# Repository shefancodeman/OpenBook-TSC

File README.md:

# TSC Openbook
 Un eBook reader format din PCB, carcasa, baterie si display, creat in AutoDesk Fusion. Fiecare component e asezat pe pcb pentru a intra corespunzator in carcasa.  
PCB-ul include:
- Battery Charge Level  
- E-Paper Display Header  
- E-Paper Drive Circuit  
- Environmental Sensor BME688  
- EPD Power  
- ESP32 C6  
- External NOR Flash 64MB  
- LDO Voltage Regulator  
- Li-Po Battery Charging Controller  
- Qwiic / Stemma QT  
- RTC Module DS3231SN  
- SD Card  
- SPI ESD Protection Lines  
- Test Pads  
- USB C connector & ESD protection  
- Voltage Supervisor + Reset & Boot / IO Button  

## BOM
| Component                     | Websites                                                                                                   | Datasheet                                                                                                    |
|-------------------------------|------------------------------------------------------------------------------------------------------------|------------------------------------------------------------------------------------------------------------|
| ESP32-C6-WROOM-1-N8           | [Mouser](https://eu.mouser.com/ProductDetail/Espressif-Systems/ESP32-C6-WROOM-1U-N8?qs=1Kr7Jg1SGW%2FzPU4G%252ByMwkA%3D%3D) | [Datasheet](https://eu.mouser.com/datasheet/2/891/Espressif_Systems_7_11_2023_esp32_c6_wroom_1_wroom-3236277.pdf) |
| USB4110-GF-A                  | [Mouser](https://eu.mouser.com/ProductDetail/Same-Sky/UJC-H-G-SMT-2-P6-TR?qs=IKkN%2F947nfApFV8T6rOqww%3D%3D) | [Datasheet](https://eu.mouser.com/datasheet/2/1628/ujc_h_g_smt_2_p6_tr-3511211.pdf)                          |
| USBLC6-2SC6Y                  | [Mouser](https://eu.mouser.com/ProductDetail/STMicroelectronics/USBLC6-2SC6Y?qs=gNDSiZmRJS%2FOgDexvXkdow%3D%3D) | [Datasheet](https://eu.mouser.com/datasheet/2/389/usblc6_2sc6y-1852505.pdf)                                   |
| DMG2305UX-7                   | [Mouser](https://eu.mouser.com/ProductDetail/Diodes-Incorporated/DMG2305UX-7?qs=L1DZKBg7t5F%2FNBHrjfxC%252Bg%3D%3D) | [Datasheet](https://www.diodes.com/assets/Datasheets/DMG2305UX.pdf)                                           |
| SD0805S020S1R0                | [Mouser](https://eu.mouser.com/ProductDetail/KYOCERA-AVX/SD0805S020S1R0?qs=jCA%252BPfw4LHbpkAoSnwrdjw%3D%3D) | [Datasheet](https://eu.mouser.com/datasheet/2/40/schottky-3165252.pdf)                                       |
| XC6220A331MR-G                | [Mouser](https://eu.mouser.com/ProductDetail/Torex-Semiconductor/XC6220A331MR-G?qs=AsjdqWjXhJ8ZSWznL1J0gg%3D%3D) | [Datasheet](https://eu.mouser.com/datasheet/2/760/xc6220-3371556.pdf)                                         |
| 293D107X9010D2TE3             | [Mouser](https://eu.mouser.com/ProductDetail/Vishay-Sprague/293D107X9010D2TE3?qs=8dfOI6wKXonVqFgS8%252BQ%2FMA%3D%3D) | [Datasheet](https://www.vishay.com/docs/40002/293d.pdf)                                                       |
| IFDC5050JZER680M              | [Mouser](https://eu.mouser.com/ProductDetail/Vishay-Dale/IFDC5050JZER680M?qs=iLKYxzqNS745SePZd8tBoA%3D%3D) | [Datasheet](https://www.vishay.com/docs/34635/ifdc5050jz.pdf)                                                |
| MBR0530-TP                    | [Mouser](https://eu.mouser.com/ProductDetail/Micro-Commercial-Components-MCC/MBR0530-TP?qs=KFo7JewZbUECRHkxGanrdg%3D%3D) | [Datasheet](https://eu.mouser.com/datasheet/2/258/MBR0520_MBR0580_SOD123_-2492194.pdf)                      |
| SI1308EDL-T1-GE3              | [Mouser](https://eu.mouser.com/ProductDetail/Vishay-Semiconductors/SI1308EDL-T1-GE3?qs=bX1%252BNvsK%2FBramh9tgpOaEw%3D%3D) | [Datasheet](https://www.vishay.com/docs/63399/si1308edl.pdf)                                                |
| KGF21BR71H104KT               | [Mouser](https://eu.mouser.com/ProductDetail/KYOCERA-AVX/KGF21BR71H104KT?qs=Jm2GQyTW%2FbjYyKCvVWAEOw%3D%3D) | [Datasheet](https://eu.mouser.com/datasheet/2/40/KGF-3223650.pdf)                                            |
| MAASL105CC7105MFCA01          | [Mouser](https://eu.mouser.com/ProductDetail/TAIYO-YUDEN/MAASL105CC7105MFCA01?qs=HFfMDpzxxd1Fn%2FInbJA7vw%3D%3D) | [Datasheet](https://eu.mouser.com/datasheet/2/396/TAIYO_YUDEN_04_27_2024_c_mlcc_A_e1-3451516.pdf)           |
| CM05X5R475M16AH               | [Mouser](https://eu.mouser.com/ProductDetail/KYOCERA-AVX/CM05X5R475M16AH?qs=doiCPypUmgFT1xquZKhWtQ%3D%3D) | [Datasheet](https://eu.mouser.com/datasheet/2/40/Kyocera_AVX_Components_CM025_CM05_CM105_CM21_E217K-2932876.pdf) |
| CGA3EDX7T1A106M080AU          | [Mouser](https://eu.mouser.com/ProductDetail/TDK/CGA3EDX7T1A106M080AU?qs=ZcfC38r4PovL%2FBNBUzzBFw%3D%3D) | [Datasheet](https://product.tdk.com/system/files/dam/doc/product/capacitor/ceramic/mlcc/catalog/mlcc_automotive_general_en.pdf) |
| KAM21BR71H104JT               | [Mouser](https://eu.mouser.com/ProductDetail/KYOCERA-AVX/KAM21BR71H104JT?qs=Jm2GQyTW%2Fbic6Zk4McEt6w%3D%3D) | [Datasheet](https://eu.mouser.com/datasheet/2/40/AutoMLCCKAM-3216307.pdf)                                    |
| RNCL1210FT50L0                | [Mouser](https://eu.mouser.com/ProductDetail/SEI-Stackpole/RNCL1210FT50L0?qs=17ckDYBRdelVLOJ%252BDFjlUw%3D%3D) | [Datasheet](https://eu.mouser.com/datasheet/2/385/sei_rncl-3223524.pdf)                                      |
| RT1206FRE072R2L               | [Mouser](https://eu.mouser.com/ProductDetail/YAGEO/RT1206FRE072R2L?qs=XhSZopxZ3H6S0nYZD83pAA%3D%3D) | [Datasheet](https://eu.mouser.com/datasheet/2/447/PYu_RT_1_to_0_01_RoHS_L_15-3461507.pdf)                    |
| ERA-6AHD150V                  | [Mouser](https://eu.mouser.com/ProductDetail/Panasonic/ERA-6AHD150V?qs=MNPzkKEzRtQip8ZeekU%252BRw%3D%3D) | [Datasheet](https://industrial.panasonic.com/cdbs/www-data/pdf/RDM0000/AOA0000C307.pdf)                     |
| RP73C2B200RFTDF               | [Mouser](https://eu.mouser.com/ProductDetail/TE-Connectivity-Holsworthy/RP73C2B200RFTDF?qs=n4i9pByFsMR0dWGpf721CA%3D%3D) | [Datasheet](https://eu.mouser.com/datasheet/2/418/10/ENG_DS_1773272_M1-1588495.pdf)                          |
| ERA-3AED202V                  | [Mouser](https://eu.mouser.com/ProductDetail/Panasonic/ERA-3AED202V?qs=yocZuyCaXdM2cBmjcGkIyA%3D%3D) | [Datasheet](https://industrial.panasonic.com/cdbs/www-data/pdf/RDM0000/AOA0000C307.pdf)                     |
| MCS04020C5101FE000            | [Mouser](https://eu.mouser.com/ProductDetail/Vishay-Beyschlag/MCS04020C5101FE000?qs=wTZ%2FFzl837YsKPLPRIXUbg%3D%3D) | [Datasheet](https://www.vishay.com/docs/28705/mcx0x0xpro.pdf)                                               |
| RNWA0612BTE10K0               | [Mouser](https://eu.mouser.com/ProductDetail/SEI-Stackpole/RNWA0612BTE10K0?qs=IKkN%2F947nfD62pDKWE9ZTQ%3D%3D) | [Datasheet](https://eu.mouser.com/datasheet/2/385/SEI_RNWA-3473840.pdf)                                      |
| ERA-3AED104V                  | [Mouser](https://eu.mouser.com/ProductDetail/Panasonic/ERA-3AED104V?qs=MNPzkKEzRtQIWcmUWL4kjg%3D%3D) | [Datasheet](https://industrial.panasonic.com/cdbs/www-data/pdf/RDM0000/AOA0000C307.pdf)                     |
| MCP73831-2ACI-MC              | [Mouser](https://eu.mouser.com/ProductDetail/Microchip-Technology/MCP73831-2ACI-MC?qs=hH%252BOa0VZEiBneYTVdpuVdg%3D%3D) | [Datasheet](https://eu.mouser.com/datasheet/2/268/MCP73831_Family_Data_Sheet_DS20001984H-3441711.pdf)       |
| FH34SRJ-24S-0.5SH(99)         | [Mouser](https://eu.mouser.com/ProductDetail/Hirose-Connector/FH34SRJ-24S-0.5SH99?qs=vcbW%252B4%252BSTIpKBl5ap9J8Fw%3D%3D) | [Datasheet](https://eu.mouser.com/datasheet/2/185/FH34SRJ_24S_0_5SH_99__CL0580_1255_6_99_2DDrawing_0-1615044.pdf) |
| BME688                        | [Mouser](https://eu.mouser.com/ProductDetail/Bosch-Sensortec/BME688?qs=IS%252B4QmGtzzqQoVDscqwx3A%3D%3D) | [Datasheet](https://eu.mouser.com/datasheet/2/783/bst_bme688_fl000-2307034.pdf)                              |
| BD5229G-TR                    | [Mouser](https://eu.mouser.com/ProductDetail/ROHM-Semiconductor/BD5229G-TR?qs=4kLU8WoGk0vvnhrrYwdszw%3D%3D) | [Datasheet](https://fscdn.rohm.com/en/products/databook/datasheet/ic/power/voltage_detector/bd52xxg-e.pdf)  |
| MAX17048G+T10                 | [Mouser](https://eu.mouser.com/ProductDetail/Analog-Devices-Maxim-Integrated/MAX17048G%2bT10?qs=D7PJwyCwLAoGnnn8jEPRBQ%3D%3D) | [Datasheet](https://eu.mouser.com/datasheet/2/609/MAX17048_MAX17049-3469099.pdf)                             |
| DS3231SN#                     | [Mouser](https://eu.mouser.com/ProductDetail/Analog-Devices-Maxim-Integrated/DS3231SN?qs=1eQvB6Dk1vhUlr8%2FOrV0Fw%3D%3D) | [Datasheet](https://eu.mouser.com/datasheet/2/609/DS3231-3421123.pdf)                                        |
| CPH3225A                      | [Mouser](https://eu.mouser.com/ProductDetail/Seiko-Semiconductors/CPH3225A?qs=3etwrb1wR%252BhUOph6lAO7eg%3D%3D) | [Datasheet](https://eu.mouser.com/datasheet/2/360/Seiko_Instruments_MicroBattery_E_20230330_2024Jan_-3561061.pdf) |
| PRT-14417                     | [Mouser](https://eu.mouser.com/ProductDetail/Adafruit/4208?qs=PzGy0jfpSMtbScLbr0L5dw%3D%3D) | [Datasheet](https://learn.adafruit.com/introducing-adafruit-stemma-qt/technical-specs)                      |
| PGB1010603MR                  | [Mouser](https://eu.mouser.com/ProductDetail/Littelfuse/PGB1010603MR?qs=gu7KAQ731URLg4GSnNNN7Q%3D%3D) | [Datasheet](https://www.littelfuse.com/assetdocs/pulseguard-esd-suppressors-pgb1-datasheet?assetguid=8a337998-d54d-466b-be4e-dc5bcd1f9321) |
| W25Q512JVEIQ                  | [Mouser](https://eu.mouser.com/ProductDetail/Winbond/W25Q512JVEIQ?qs=l7cgNqFNU1jw6svr3at6tA%3D%3D) | [Datasheet](https://eu.mouser.com/datasheet/2/949/Winbond_W25Q512JV_Datasheet-3240039.pdf)                   |
| MT-DEPG0750BNU590F1           | [Mouser](https://eu.mouser.com/ProductDetail/Microtips-Technology/MT-DEPG0750BNU590F1?qs=DPoM0jnrROVRMMTX0WzK%252Bw%3D%3D) | [Datasheet](https://eu.mouser.com/datasheet/2/271/MT_DEPG0750BNU590F1_V2_7-1894282.pdf)                     |
| 112A-TAAR-R03                 | [Comet](https://store.comet.srl.ro/Catalogue/Product/43497/)                                               | [Datasheet](https://store.comet.bg/download-file.php?id=27596)                                                |
| LP584174                      | [TME](https://www.tme.eu/en/details/accu-lp584174_cl/rechargeable-batteries/cellevia-batteries/l584174/) | [Datasheet](https://www.tme.eu/Document/e0683d8c34e6d878124489f71bffb6ee/cel0014.pdf)                        |

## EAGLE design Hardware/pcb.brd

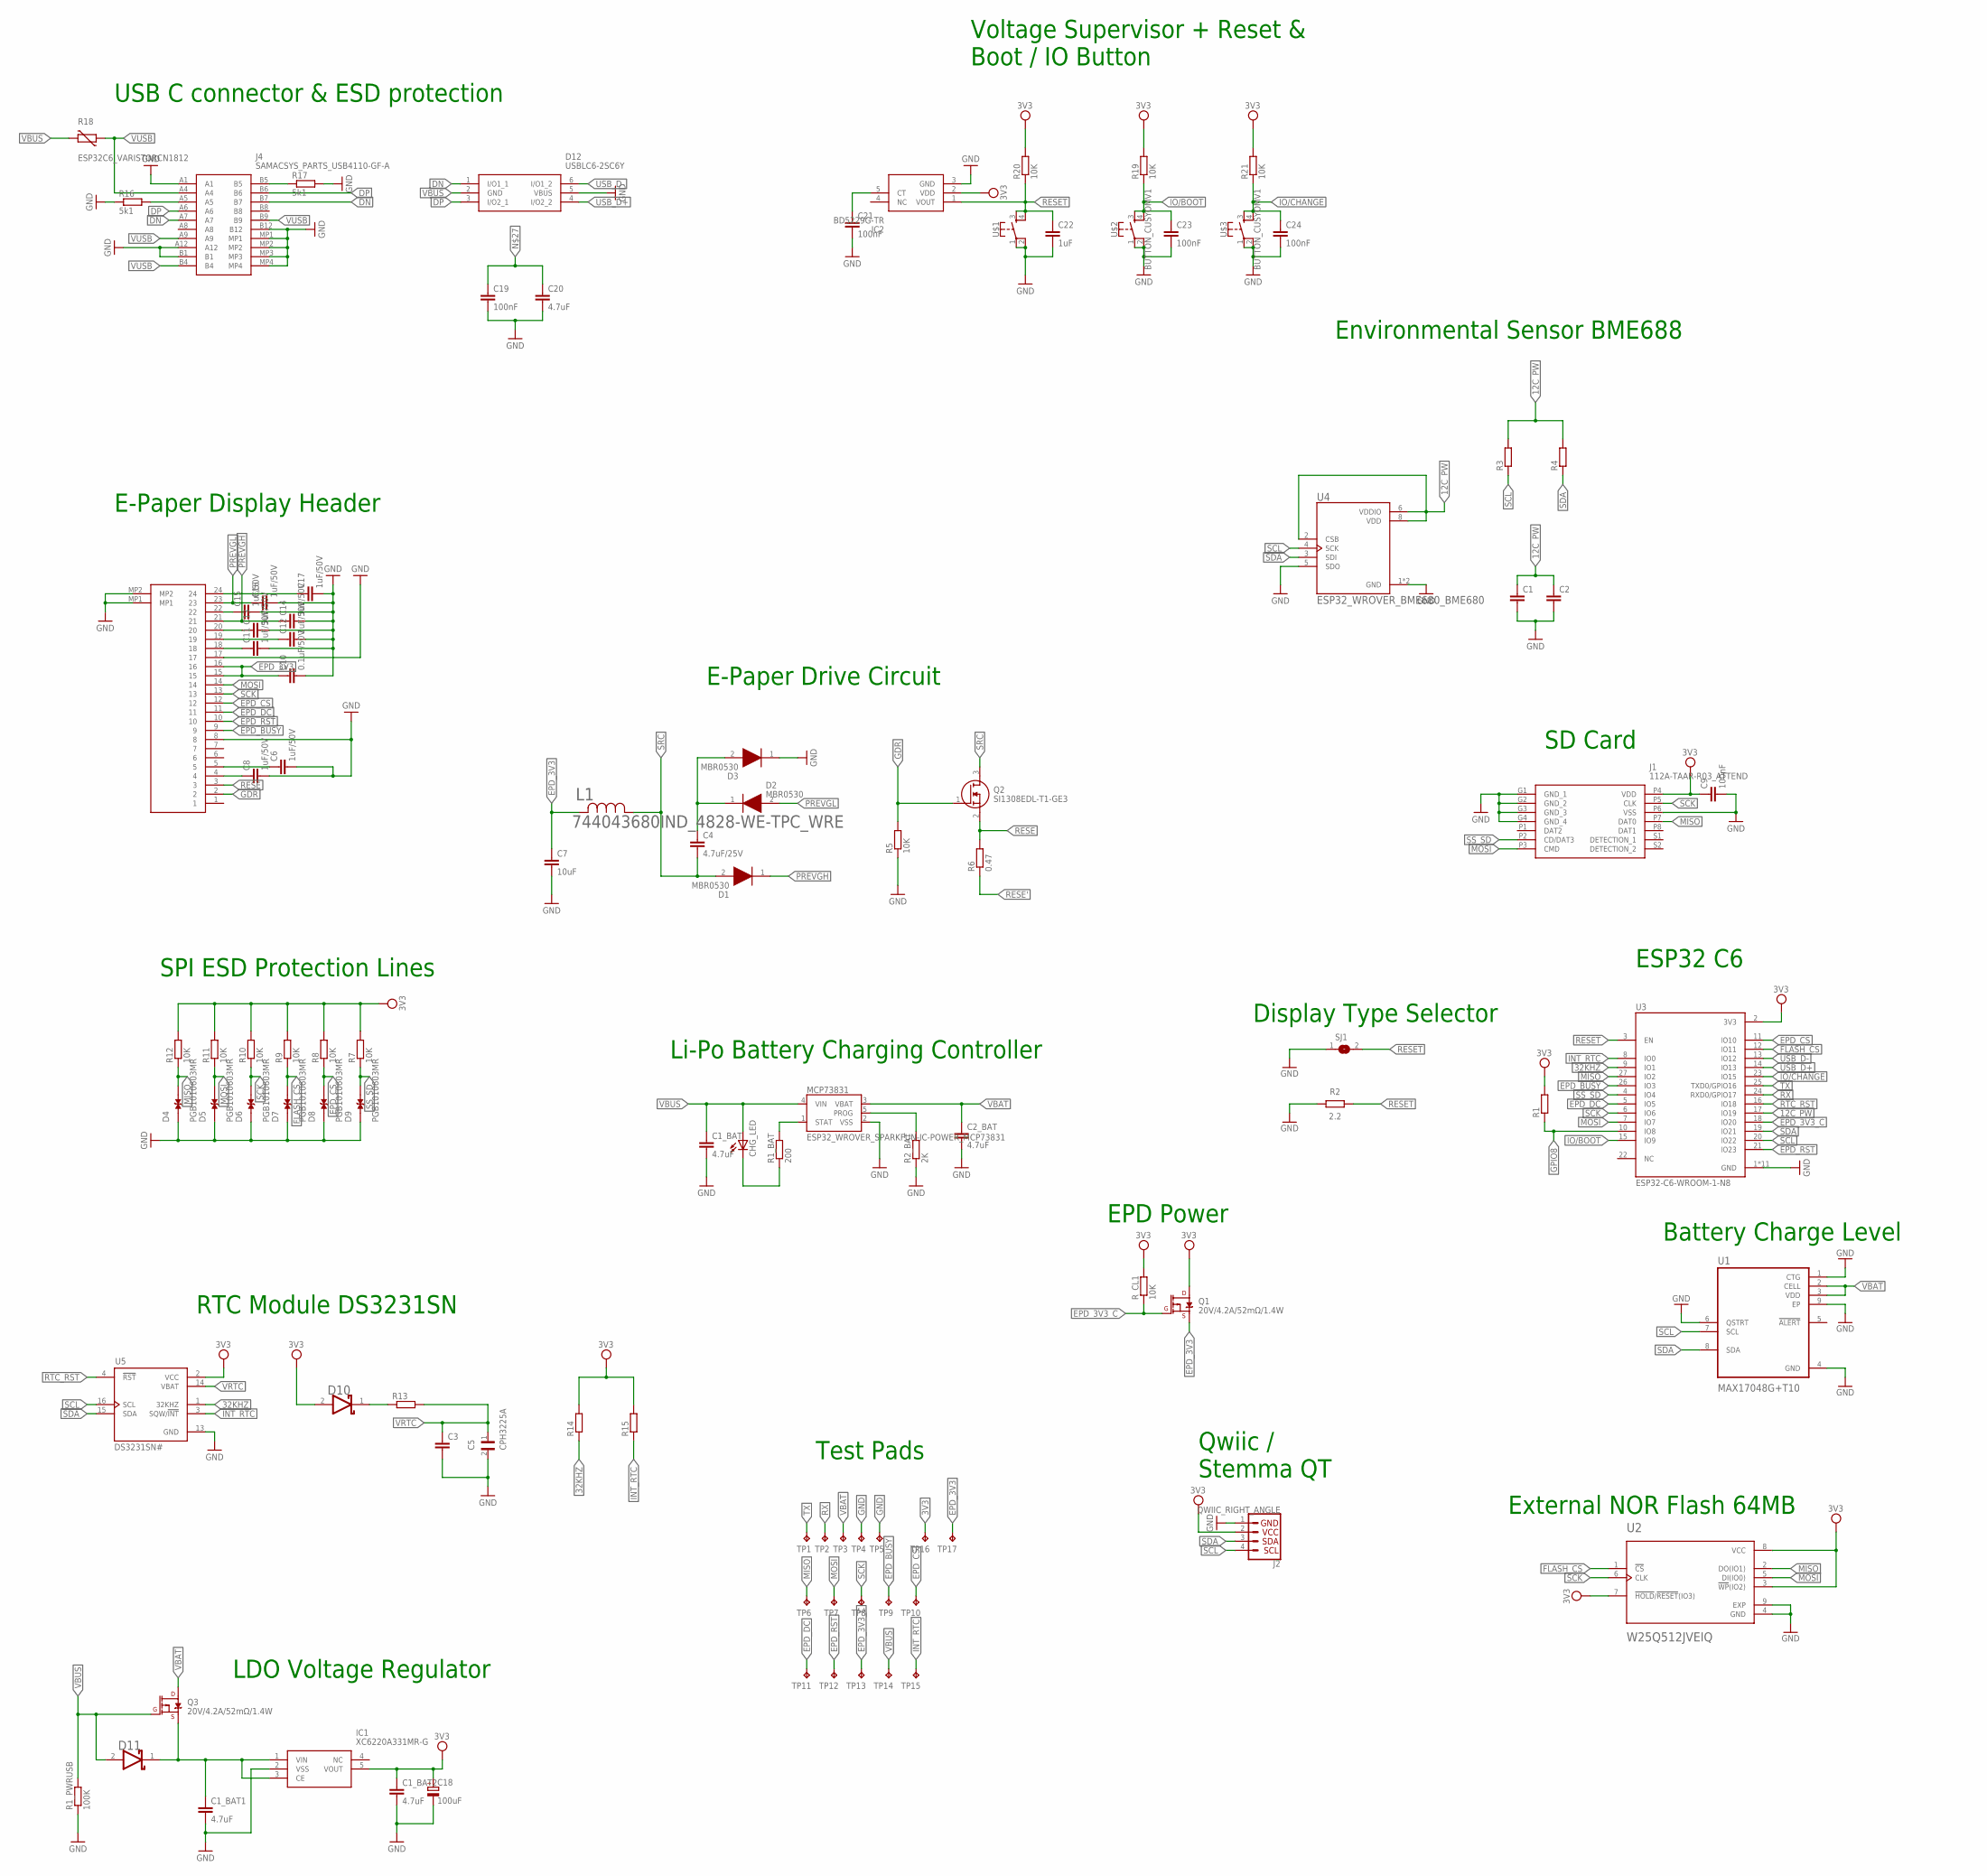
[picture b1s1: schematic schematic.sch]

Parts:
C1, C2: ESP32_WROVER_EAGLE-LTSPICE_CC0402; ESP32_WROVER_EAGLE-LTSPICE_C0402
C1_BAT, C1_BAT1, C1_BAT2, C2_BAT, C20: 4.7uF; ESP32_WROVER_EAGLE-LTSPICE_C0402
C3: EAGLE-LTSPICE_CC0402; EAGLE-LTSPICE_C0402
C4: 4.7uF/25V; EAGLE-LTSPICE_C0402
C5: CPH3225A; CAPCP3225X100N
C6, C8, C11, C12, C13, C14, C15, C16, C17: 1uF/50V; ESP32_WROVER_EAGLE-LTSPICE_C0402
C7: 10uF; EAGLE-LTSPICE_C0402
C9: 100nF; EAGLE-LTSPICE_C0402
C10: 0.1uF/50V; ESP32_WROVER_EAGLE-LTSPICE_C0402
C18: 100uF; RCL_CT3528
C19, C21, C23, C24: 100nF; ESP32_WROVER_EAGLE-LTSPICE_C0402
C22: 1uF; ESP32_WROVER_EAGLE-LTSPICE_C0402
CHG_LED: ADAFRUIT_LEDCHIP-LED0603; ADAFRUIT_CHIP-LED0603
D1, D2, D3: MBR0530; SOD3716X135N
D4, D5, D6, D7, D8, D9: PGB1010603MR; DIOC1608X36N
D10, D11: ESP32_WROVER_AVX---SD0805S020S1R0_AVX_SD0805S020S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; ESP32_WROVER_AVX---SD0805S020S1R0_AVX_SD0805S020S1R0_0
D12: USBLC6-2SC6Y; SOT95P280X145-6N
IC1: XC6220A331MR-G; SOT95P280X120-5N
IC2: BD5229G-TR; SOT95P280X125-5N
J1: 112A-TAAR-R03_ATTEND; 112ATAARR03ATTEND
J2: QWIIC_RIGHT_ANGLE; JST04_1MM_RA
J3: FH34SRJ-24S-0.5SH_99_; FH34SRJ24S05SH99
J4: SAMACSYS_PARTS_USB4110-GF-A; SAMACSYS_PARTS_USB4110GFA
L1: 744043680IND_4828-WE-TPC_WRE; IND_4828-WE-TPC_WRE
MCP73831: ESP32_WROVER_SPARKFUN-IC-POWER_MCP73831; ESP32_WROVER_SPARKFUN-IC-POWER_SOT23-5
Q1, Q3: 20V/4.2A/52mΩ/1.4W; ESP32_WROVER_SPARKFUN-DISCRETESEMI_SOT23-3
Q2: SI1308EDL-T1-GE3; SOT65P210X110-3N
R1, R3, R4, R13, R14, R15: ESP32_WROVER_EAGLE-LTSPICE_RR0402; ESP32_WROVER_EAGLE-LTSPICE_R0402
R1_BAT: 200; ESP32_WROVER_EAGLE-LTSPICE_R0402
R1_PWRUSB: 100K; ESP32_WROVER_EAGLE-LTSPICE_R0402
R2: 2.2; RESC1005X40
R2_BAT: 2K; ESP32_WROVER_EAGLE-LTSPICE_R0402
R5, R7, R8, R9, R10, R11, R12, R19, R20, R21: 10K; ESP32_WROVER_EAGLE-LTSPICE_R0402
R6: 0.47; ESP32_WROVER_EAGLE-LTSPICE_R0402
R16, R17: 5k1; ESP32_WROVER_EAGLE-LTSPICE_R0402
R18: ESP32C6_VARISTORCN1812; ESP32C6_VARISTOR_CT/CN1812
R_CL1: 10K; ESP32_WROVER_EAGLE-LTSPICE_R0402
SJ1: SJ
TP1, TP2, TP3, TP4, TP5, TP6, TP7, TP8, TP9, TP10, TP11, TP12, TP13, TP14, TP15, TP16, TP17: TPTP20R; TP20R
U1: MAX17048G+T10; SON50P200X200X80-9N
U2: W25Q512JVEIQ; SON127P600X800X80-9N
U3: ESP32-C6-WROOM-1-N8; XCVR_ESP32-C6-WROOM-1-N8
U4: ESP32_WROVER_BME680_BME680; ESP32_WROVER_BME680_PSON80P300X300X100-8N
U5: DS3231SN#; SOIC127P1032X265-16N
U$1, U$2, U$3: BUTTON_CUSYOMV1; MYBUTTON

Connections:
3V3: C1_BAT2.1, C9.1, C18.+, D10.2 (ANODE), IC1.5 (VOUT), IC2.2 (VDD), J1.P4 (VDD), J2.2, Q1.3 (D), R1.2, R7.2, R8.2, R9.2, R10.2, R11.2, R12.2, R14.2, R15.2, R19.2, R20.2, R21.2, R_CL1.2, TP16.TP, U2.3 (!WP!(IO2)), U2.7 (!HOLD!/!RESET!(IO3)), U2.8 (VCC), U3.2 (3V3), U5.2 (VCC)
12C_PW: C1.1, C2.1, R3.2, R4.2, U3.17 (IO19), U4.2 (CSB), U4.6 (VDDIO), U4.8 (VDD)
32KHZ: R14.1, U3.9 (IO1), U5.1 (32KHZ)
DN: D12.1 (I/O1_1), J4.A7, J4.B7
DP: D12.3 (I/O2_1), J4.A6, J4.B6
EPD_3V3: C7.1, C10.1, J3.15, J3.16, L1.2, Q1.2 (S), TP17.TP
EPD_3V3_C: Q1.1 (G), R_CL1.1, TP13.TP, U3.18 (IO20)
EPD_BUSY: J3.9, TP9.TP, U3.26 (IO3)
EPD_CS: D8.2, J3.12, R8.1, TP10.TP, U3.11 (IO10)
EPD_DC: J3.11, TP11.TP, U3.5 (IO5)
EPD_RST: J3.10, TP12.TP, U3.21 (IO23)
FLASH_CS: D7.2, R9.1, U2.1 (!CS), U3.12 (IO11)
GDR: J3.2, Q2.1 (G), R5.2
GND: C1.2, C1_BAT.2, C1_BAT1.2, C1_BAT2.2, C2.2, C2_BAT.2, C3.2, C5.2, C6.2, C7.2, C8.2, C9.2, C10.2, C11.2, C12.2, C13.2, C14.2, C15.2, C16.2, C17.2, C18.-, C19.2, C20.2, C21.2, C22.2, C23.2, C24.2, D3.1 (K), D4.1, D5.1, D6.1, D7.1, D8.1, D9.1, D12.5 (VBUS), IC1.2 (VSS), IC2.3 (GND), J1.G1 (GND_1), J1.G2 (GND_2), J1.G3 (GND_3), J1.G4 (GND_4), J1.P6 (VSS), J2.1, J3.8, J3.17, J3.MP1, J3.MP2, J4.A1, J4.A12, J4.B1, J4.B12, J4.MP1, J4.MP2, J4.MP3, J4.MP4, MCP73831.2 (VSS), R1_PWRUSB.1, R2.1, R2_BAT.1, R5.1, R16.1, R17.2, SJ1.1, TP4.TP, TP5.TP, U1.1 (CTG), U1.4 (GND), U1.6 (QSTRT), U1.9 (EP), U2.4 (GND), U2.9 (EXP), U3.1 (GND), U3.28 (GND), U3.29_1 (GND), U3.29_2 (GND), U3.29_3 (GND), U3.29_4 (GND), U3.29_5 (GND), U3.29_6 (GND), U3.29_7 (GND), U3.29_8 (GND), U3.29_9 (GND), U4.1 (GND), U4.5 (SDO), U4.7 (GND), U5.13 (GND), U$1.1, U$1.2, U$2.1, U$2.2, U$3.1, U$3.2
GPIO8: R1.1, U3.10 (IO8)
INT_RTC: R15.1, TP15.TP, U3.8 (IO0), U5.3 (SQW/!INT)
IO/BOOT: C23.1, R19.1, U3.15 (IO9), U$2.3, U$2.4
IO/CHANGE: C24.1, R21.1, U3.23 (IO15), U$3.3, U$3.4
MISO: D4.2, J1.P7 (DAT0), R12.1, TP6.TP, U2.2 (DO(IO1)), U3.27 (IO2)
MOSI: D5.2, J1.P3 (CMD), J3.14, R11.1, TP7.TP, U2.5 (DI(IO0)), U3.7 (IO7)
unnamed: C4.1, D2.1 (K), D3.2 (A)
unnamed: MCP73831.1 (STAT), R1_BAT.2
unnamed: CHG_LED.C, R1_BAT.1
unnamed: C1_BAT1.1, D11.1 (CATHODE), IC1.1 (VIN), IC1.3 (CE), Q3.2 (S)
unnamed: MCP73831.5 (PROG), R2_BAT.2
unnamed: C17.1, J3.24
unnamed: C21.1, IC2.5 (CT)
unnamed: C15.1, J3.22
unnamed: C13.1, J3.20
unnamed: D10.1 (CATHODE), R13.1
unnamed: C12.1, J3.19
unnamed: C11.1, J3.18
unnamed: C6.1, J3.5
unnamed: C8.1, J3.4
unnamed: J4.A5, R16.2
unnamed: C19.1, C20.1
unnamed: J4.B5, R17.1
PREVGH: C14.1, D1.1 (K), J3.21
PREVGL: C16.1, D2.2 (A), J3.23
RESE: J3.3, Q2.2 (S), R6.2
RESE': R6.1
RESET: C22.1, IC2.1 (VOUT), R2.2, R20.1, SJ1.2, U3.3 (EN), U$1.3, U$1.4
RTC_RST: U3.16 (IO18), U5.4 (!RST)
RX: TP2.TP, U3.24 (RXD0/GPIO17)
SCK: D6.2, J1.P5 (CLK), J3.13, R10.1, TP8.TP, U2.6 (CLK), U3.6 (IO6)
SCL: J2.4, R3.1, U1.7 (SCL), U3.20 (IO22), U4.4 (SCK), U5.16 (SCL)
SDA: J2.3, R4.1, U1.8 (SDA), U3.19 (IO21), U4.3 (SDI), U5.15 (SDA)
SRC: C4.2, D1.2 (A), L1.1, Q2.3 (D)
SS_SD: D9.2, J1.P2 (CD/DAT3), R7.1, U3.4 (IO4)
TX: TP1.TP, U3.25 (TXD0/GPIO16)
USB_D+: D12.4 (I/O2_2), U3.14 (IO13)
USB_D-: D12.6 (I/O1_2), U3.13 (IO12)
VBAT: C2_BAT.1, MCP73831.3 (VBAT), Q3.3 (D), TP3.TP, U1.2 (CELL), U1.3 (VDD)
VBUS: C1_BAT.1, CHG_LED.A, D11.2 (ANODE), D12.2 (GND), MCP73831.4 (VIN), Q3.1 (G), R1_PWRUSB.2, R18.2, TP14.TP
VRTC: C3.1, C5.1, R13.2, U5.14 (VBAT)
VUSB: J4.A4, J4.A9, J4.B4, J4.B9, R18.1

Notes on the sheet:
USB C connector & ESD protection
Voltage Supervisor + Reset & Boot / IO Button
Environmental Sensor BME688
SD Card
E-Paper Display Header
SPI ESD Protection Lines
E-Paper Drive Circuit
ESP32 C6
Battery Charge Level
External NOR Flash 64MB
Qwiic / Stemma QT
Li-Po Battery Charging Controller
Display Type Selector
EPD Power
Test Pads
RTC Module DS3231SN
LDO Voltage Regulator

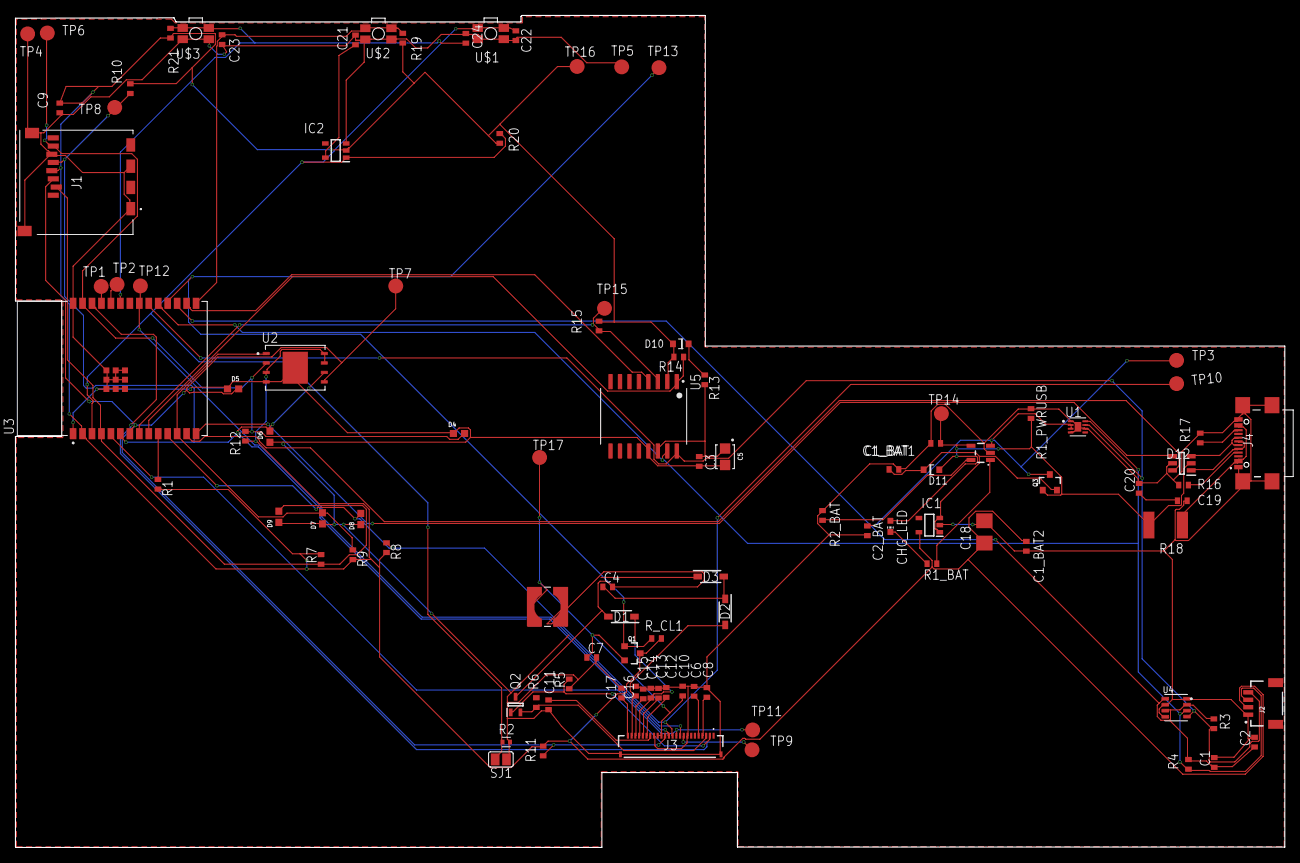
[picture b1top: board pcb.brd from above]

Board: 2 copper layers, 170.4 x 111.7 mm, 103 parts (0 on the bottom side), 55 nets.

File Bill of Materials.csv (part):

Part,Value,Device,Package,Description,ARROW_PART_NUMBER,ARROW_PRICE-STOCK,AVAILABILITY,CATEGORY,CENTROID_NOT_SPECIFIED,CHECK_PRICES,COPYRIGHT,DATASHEET,DESCRIPTION,DIGIKEY_DESCRIPTION,DIGIKEY_PART_NUMBER,HEIGHT,LEAD_FREE,MANUFACTURER,MANUFACTURER_NAME,MANUFACTURER_PART_NUMBER,MF,MFR_NAME,MOUSER_PART_NUMBER,MOUSER_PRICE-STOCK,MOUSER_TESTING_PART_NUMBER,MOUSER_TESTING_PRICE-STOCK,MP,MPN,OPERATING_TEMPERATURE,PACKAGE,PACKAGE_SIZE,PACKAGE_TYPE,PART_STATUS,POPULARITY,PREFIX,PRICE,PROD_ID,PURCHASE-URL,ROHS,SERIES,SNAPEDA_LINK,SPICEMODEL,SPICEPREFIX,SUBCATEGORY,TEMPERATURE_COEFFICIENT,TEMPERATURE_RANGE_HIGH,TEMPERATURE_RANGE_LOW,THERMALLOSS,TOLERANCE,TP_SIGNAL_NAME,TYPE,VALUE
C1,,ESP32_WROVER_EAGLE-LTSPICE_CC0402,ESP32_WROVER_EAGLE-LTSPICE_C0402,"CAPACITOR, European symbol",,,,,,,,,,,,,,,,,,,,,,,,,,,,,,,,,,,,,,NONE,C,,,,,,,,,
C1_BAT,4.7uF,ESP32_WROVER_EAGLE-LTSPICE_CC0402,ESP32_WROVER_EAGLE-LTSPICE_C0402,"CAPACITOR, European symbol",,,,,,,,,,,,,,,,,,,,,,,,,,,,,,,,,,,,,,NONE,C,,,,,,,,,
C1_BAT1,4.7uF,ESP32_WROVER_EAGLE-LTSPICE_CC0402,ESP32_WROVER_EAGLE-LTSPICE_C0402,"CAPACITOR, European symbol",,,,,,,,,,,,,,,,,,,,,,,,,,,,,,,,,,,,,,NONE,C,,,,,,,,,
C1_BAT2,4.7uF,ESP32_WROVER_EAGLE-LTSPICE_CC0402,ESP32_WROVER_EAGLE-LTSPICE_C0402,"CAPACITOR, European symbol",,,,,,,,,,,,,,,,,,,,,,,,,,,,,,,,,,,,,,NONE,C,,,,,,,,,
C2,,ESP32_WROVER_EAGLE-LTSPICE_CC0402,ESP32_WROVER_EAGLE-LTSPICE_C0402,"CAPACITOR, European symbol",,,,,,,,,,,,,,,,,,,,,,,,,,,,,,,,,,,,,,NONE,C,,,,,,,,,
C2_BAT,4.7uF,ESP32_WROVER_EAGLE-LTSPICE_CC0402,ESP32_WROVER_EAGLE-LTSPICE_C0402,"CAPACITOR, European symbol",,,,,,,,,,,,,,,,,,,,,,,,,,,,,,,,,,,,,,NONE,C,,,,,,,,,
C3,,EAGLE-LTSPICE_CC0402,EAGLE-LTSPICE_C0402,"CAPACITOR, European symbol",,,,,,,,,,,,,,,,,,,,,,,,,,,,,,,,,,,,,,NONE,C,,,,,,,,,
C4,4.7uF/25V,EAGLE-LTSPICE_CC0402,EAGLE-LTSPICE_C0402,"CAPACITOR, European symbol",,,,,,,,,,,,,,,,,,,,,,,,,,,,,,,,,,,,,,NONE,C,,,,,,,,,
C5,CPH3225A,CPH3225A,CAPCP3225X100N,"Cap 0.011F 3.3V 1210 Flat Check availability",,,"Not in stock",,,https://www.snapeda.com/parts/CPH3225A/Seiko+Instruments/vie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,,," 11 mF (EDLC) Supercapacitor 3.3 V 1210 (3225 Metric) - - ",,,,,,,,"Seiko Instruments",,,,,,CPH3225A,,,"1210 Seiko",,,,,,None,,"https://www.snapeda.com/api/url_track_click_mouser/?unipart_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 Instruments&part_name=CPH3225A&search_term=None",,,https://www.snapeda.com/parts/CPH3225A/Seiko+Instruments/vie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,,,,,,,,,,,
C6,1uF/50V,ESP32_WROVER_EAGLE-LTSPICE_CC0402,ESP32_WROVER_EAGLE-LTSPICE_C0402,"CAPACITOR, European symbol",,,,,,,,,,,,,,,,,,,,,,,,,,,,,,,,,,,,,,NONE,C,,,,,,,,,
C7,10uF,EAGLE-LTSPICE_CC0402,EAGLE-LTSPICE_C0402,"CAPACITOR, European symbol",,,,,,,,,,,,,,,,,,,,,,,,,,,,,,,,,,,,,,NONE,C,,,,,,,,,
C8,1uF/50V,ESP32_WROVER_EAGLE-LTSPICE_CC0402,ESP32_WROVER_EAGLE-LTSPICE_C0402,"CAPACITOR, European symbol",,,,,,,,,,,,,,,,,,,,,,,,,,,,,,,,,,,,,,NONE,C,,,,,,,,,
C9,100nF,EAGLE-LTSPICE_CC0402,EAGLE-LTSPICE_C0402,"CAPACITOR, European symbol",,,,,,,,,,,,,,,,,,,,,,,,,,,,,,,,,,,,,,NONE,C,,,,,,,,,
C10,0.1uF/50V,ESP32_WROVER_EAGLE-LTSPICE_CC0402,ESP32_WROVER_EAGLE-LTSPICE_C0402,"CAPACITOR, European symbol",,,,,,,,,,,,,,,,,,,,,,,,,,,,,,,,,,,,,,NONE,C,,,,,,,,,
C11,1uF/50V,ESP32_WROVER_EAGLE-LTSPICE_CC0402,ESP32_WROVER_EAGLE-LTSPICE_C0402,"CAPACITOR, European symbol",,,,,,,,,,,,,,,,,,,,,,,,,,,,,,,,,,,,,,NONE,C,,,,,,,,,
C12,1uF/50V,ESP32_WROVER_EAGLE-LTSPICE_CC0402,ESP32_WROVER_EAGLE-LTSPICE_C0402,"CAPACITOR, European symbol",,,,,,,,,,,,,,,,,,,,,,,,,,,,,,,,,,,,,,NONE,C,,,,,,,,,
C13,1uF/50V,ESP32_WROVER_EAGLE-LTSPICE_CC0402,ESP32_WROVER_EAGLE-LTSPICE_C0402,"CAPACITOR, European symbol",,,,,,,,,,,,,,,,,,,,,,,,,,,,,,,,,,,,,,NONE,C,,,,,,,,,
C14,1uF/50V,ESP32_WROVER_EAGLE-LTSPICE_CC0402,ESP32_WROVER_EAGLE-LTSPICE_C0402,"CAPACITOR, European symbol",,,,,,,,,,,,,,,,,,,,,,,,,,,,,,,,,,,,,,NONE,C,,,,,,,,,
C15,1uF/50V,ESP32_WROVER_EAGLE-LTSPICE_CC0402,ESP32_WROVER_EAGLE-LTSPICE_C0402,"CAPACITOR, European symbol",,,,,,,,,,,,,,,,,,,,,,,,,,,,,,,,,,,,,,NONE,C,,,,,,,,,
C16,1uF/50V,ESP32_WROVER_EAGLE-LTSPICE_CC0402,ESP32_WROVER_EAGLE-LTSPICE_C0402,"CAPACITOR, European symbol",,,,,,,,,,,,,,,,,,,,,,,,,,,,,,,,,,,,,,NONE,C,,,,,,,,,
C17,1uF/50V,ESP32_WROVER_EAGLE-LTSPICE_CC0402,ESP32_WROVER_EAGLE-LTSPICE_C0402,"CAPACITOR, European symbol",,,,,,,,,,,,,,,,,,,,,,,,,,,,,,,,,,,,,,NONE,C,,,,,,,,,
C18,100uF,RCL_CPOL-EUCT3528,RCL_CT3528,"POLARIZED CAPACITOR, European symbol",,,,,,,,,,,,,,,,,,,,,,,,,,,,,,0,,,,,,,,,C,,,,,,,,,
C19,100nF,ESP32_WROVER_EAGLE-LTSPICE_CC0402,ESP32_WROVER_EAGLE-LTSPICE_C0402,"CAPACITOR, European symbol",,,,,,,,,,,,,,,,,,,,,,,,,,,,,,,,,,,,,,NONE,C,,,,,,,,,
C20,4.7uF,ESP32_WROVER_EAGLE-LTSPICE_CC0402,ESP32_WROVER_EAGLE-LTSPICE_C0402,"CAPACITOR, European symbol",,,,,,,,,,,,,,,,,,,,,,,,,,,,,,,,,,,,,,NONE,C,,,,,,,,,
C21,100nF,ESP32_WROVER_EAGLE-LTSPICE_CC0402,ESP32_WROVER_EAGLE-LTSPICE_C0402,"CAPACITOR, European symbol",,,,,,,,,,,,,,,,,,,,,,,,,,,,,,,,,,,,,,NONE,C,,,,,,,,,
C22,1uF,ESP32_WROVER_EAGLE-LTSPICE_CC0402,ESP32_WROVER_EAGLE-LTSPICE_C0402,"CAPACITOR, European symbol",,,,,,,,,,,,,,,,,,,,,,,,,,,,,,,,,,,,,,NONE,C,,,,,,,,,
C23,100nF,ESP32_WROVER_EAGLE-LTSPICE_CC0402,ESP32_WROVER_EAGLE-LTSPICE_C0402,"CAPACITOR, European symbol",,,,,,,,,,,,,,,,,,,,,,,,,,,,,,,,,,,,,,NONE,C,,,,,,,,,
C24,100nF,ESP32_WROVER_EAGLE-LTSPICE_CC0402,ESP32_WROVER_EAGLE-LTSPICE_C0402,"CAPACITOR, European symbol",,,,,,,,,,,,,,,,,,,,,,,,,,,,,,,,,,,,,,NONE,C,,,,,,,,,
CHG_LED,,ADAFRUIT_LEDCHIP-LED0603,ADAFRUIT_CHIP-LED0603,LED,,,,,,,,,,,,,,,,,,,,,,,,,,,,,,,,,,,,,,,,,,,,,,,,
D1,MBR0530,MBR0530,SOD3716X135N,"ON SEMICONDUCTOR - MBR0530 - DIODE, SCHOTTKY, 0.5A, 30V, SOD-123",,,"In Stock",,,https://www.snapeda.com/parts/MBR0530/Onsemi/view-part/?ref=eda,,," Diode Schottky 30 V 500mA Surface Mount SOD-123 ",,,,,,,,"ON Semiconductor",,,,,,MBR0530,,,"SOD-123-2 ON Semiconductor",,,,,,None,,"https://www.snapeda.com/api/url_track_click_mouser/?unipart_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 Semiconductor&part_name=MBR0530&search_term=None",,,https://www.snapeda.com/parts/MBR0530/Onsemi/view-part/?ref=snap,,,,,,,,,,,
D2,MBR0530,MBR0530,SOD3716X135N,"ON SEMICONDUCTOR - MBR0530 - DIODE, SCHOTTKY, 0.5A, 30V, SOD-123",,,"In Stock",,,https://www.snapeda.com/parts/MBR0530/Onsemi/view-part/?ref=eda,,," Diode Schottky 30 V 500mA Surface Mount SOD-123 ",,,,,,,,"ON Semiconductor",,,,,,MBR0530,,,"SOD-123-2 ON Semiconductor",,,,,,None,,"https://www.snapeda.com/api/url_track_click_mouser/?unipart_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 Semiconductor&part_name=MBR0530&search_term=None",,,https://www.snapeda.com/parts/MBR0530/Onsemi/view-part/?ref=snap,,,,,,,,,,,
D3,MBR0530,MBR0530,SOD3716X135N,"ON SEMICONDUCTOR - MBR0530 - DIODE, SCHOTTKY, 0.5A, 30V, SOD-123",,,"In Stock",,,https://www.snapeda.com/parts/MBR0530/Onsemi/view-part/?ref=eda,,," Diode Schottky 30 V 500mA Surface Mount SOD-123 ",,,,,,,,"ON Semiconductor",,,,,,MBR0530,,,"SOD-123-2 ON Semiconductor",,,,,,None,,"https://www.snapeda.com/api/url_track_click_mouser/?unipart_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 Semiconductor&part_name=MBR0530&search_term=None",,,https://www.snapeda.com/parts/MBR0530/Onsemi/view-part/?ref=snap,,,,,,,,,,,
D4,PGB1010603MR,PGB1010603MR,DIOC1608X36N,"Check availability",,,"In Stock",,,https://www.snapeda.com/parts/PGB1010603MR/Littelfuse/view-p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,,," 150V (Typ) Clamp - Ipp Tvs Diode Surface Mount 0603 (1608 Metric) ",,,,,,,,"Littelfuse Inc.",,,,,,PGB1010603MR,,,"0603 Littelfuse Inc.",,,,,,None,,"https://www.snapeda.com/api/url_track_click_mouser/?unipart_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 Inc.&part_name=PGB1010603MR&search_term=None",,,https://www.snapeda.com/parts/PGB1010603MR/Littelfuse/view-p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,,,,,,,,,,,
D5,PGB1010603MR,PGB1010603MR,DIOC1608X36N,"Check availability",,,"In Stock",,,https://www.snapeda.com/parts/PGB1010603MR/Littelfuse/view-p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,,," 150V (Typ) Clamp - Ipp Tvs Diode Surface Mount 0603 (1608 Metric) ",,,,,,,,"Littelfuse Inc.",,,,,,PGB1010603MR,,,"0603 Littelfuse Inc.",,,,,,None,,"https://www.snapeda.com/api/url_track_click_mouser/?unipart_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 Inc.&part_name=PGB1010603MR&search_term=None",,,https://www.snapeda.com/parts/PGB1010603MR/Littelfuse/view-p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,,,,,,,,,,,
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
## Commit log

2025-03-22 All components done
    Recreated all components, now positioning and assembly is required
2025-03-25 Last changes regarding components, board changes
    Added last changes to components (not a lot, just moving around), board has been measured and is ready to cut. Placement is needed
2025-03-25 Deleted old version
    Deleted v5 to make way for v6
2025-03-25 Deleted old files, uploaded new ones
2025-03-25 Delete EBook READER v4 - Board.fbrd
    Deleted old version
2025-03-25 Delete EBook READER v6 - components.fsch
    Deleted old version - remeasured and cut the pcb since
2025-03-30 Project almost ready, besides ReadMe
    Created the 3D files for battery and display and combined them into a full product
2025-03-30 Delete EBook READER v7 - PCB.fbrd
    Deleted old file
2025-03-30 Delete EBook READER v8 - schematic.fsch
    Deleted old file
2025-04-03 3D models not permitted withou custom models
    I cannot upload 3D PCB model as FUSION doesn't allow bulk download of custom models. Without those models, the PCB cannot be uploaded
2025-04-03 The 3D file finally uploaded
2025-04-11 Deleted files
    Needed to clear out the repo in order to upload new files
2025-04-11 Deleted everything just to reupload
    Uploaded every file with the required formatting
2025-04-11 Am realizat ca nu am copiat repo-ul deloc
    Am aliniat butoanele, si am completat issue-urile
2025-04-11 Images updated
    Din moment ce am mutat butoanele, am updatat imaginile pentru a reflecta asta
2025-04-12 Added License file
    Last step is updating README

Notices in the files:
parts and their libraries:
COPYRIGHT: Copyright (C) 2024 Ultra Librarian. All rights reserved.
